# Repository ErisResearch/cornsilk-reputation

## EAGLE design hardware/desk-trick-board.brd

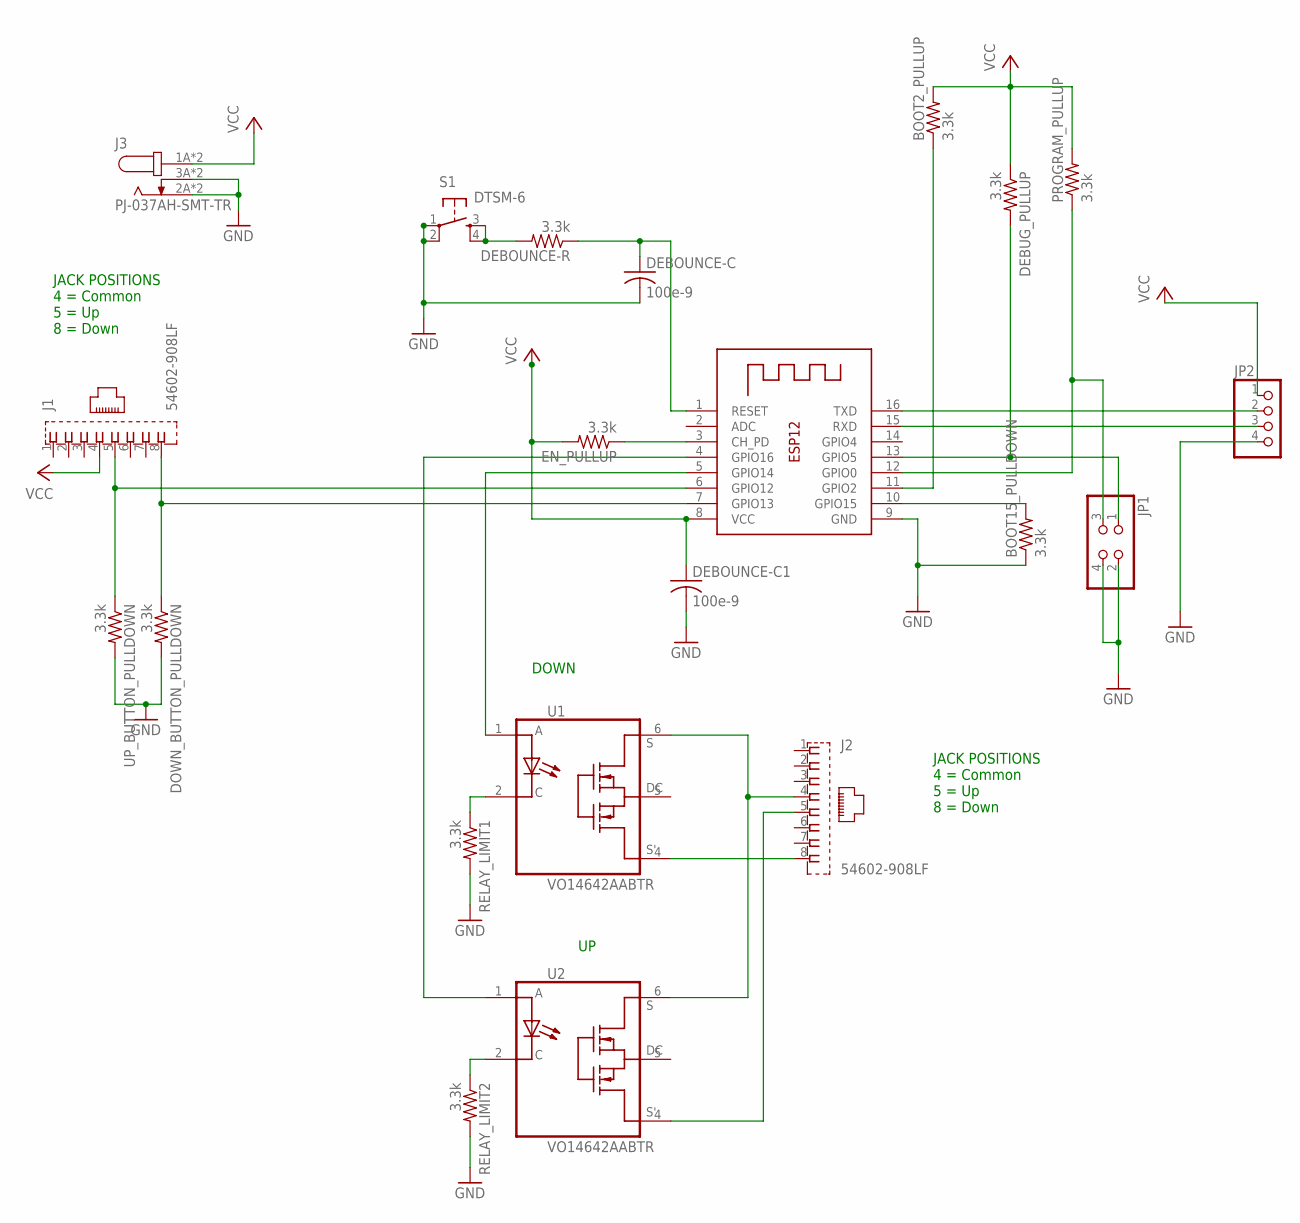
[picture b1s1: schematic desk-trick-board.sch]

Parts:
BOOT2_PULLUP, BOOT15_PULLDOWN: 3.3k; R0603
DEBOUNCE-C, DEBOUNCE-C1: 100e-9; C0603
DEBOUNCE-R: 3.3k; R0603
DEBUG_PULLUP: 3.3k; R0603
DOWN_BUTTON_PULLDOWN: 3.3k; R0603
EN_PULLUP: 3.3k; R0603
J1, J2: 54602-908LF; AMPHENOL_54602-908LF
J3: PJ-037AH-SMT-TR; CUI_PJ-037AH-SMT-TR
JP1: PINHD-2X2; 2X02
JP2: PINHD-1X4; 1X04
PROGRAM_PULLUP: 3.3k; R0603
RELAY_LIMIT1, RELAY_LIMIT2: 3.3k; R0603
S1: DTSM-6
U1, U2: VO14642AABTR; SOIC254P1005X390-6N
UP_BUTTON_PULLDOWN: 3.3k; R0603
X1: ESP-12

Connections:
BOOT2: BOOT2_PULLUP.1, X1.11 (GPIO2)
BOOT15: BOOT15_PULLDOWN.2, X1.10 (GPIO15)
DEBUG: DEBUG_PULLUP.2, JP1.1, X1.13 (GPIO5)
ESPRX: JP2.3, X1.15 (RXD)
ESPTX: JP2.2, X1.16 (TXD)
ESP_EN: EN_PULLUP.1, X1.3 (CH_PD)
GND: BOOT15_PULLDOWN.1, DEBOUNCE-C.2, DEBOUNCE-C1.2, DOWN_BUTTON_PULLDOWN.2, J3.2A (2), J3.2B (2), J3.3A (3), J3.3B (3), JP1.2, JP1.4, JP2.4, RELAY_LIMIT1.2, RELAY_LIMIT2.2, S1.1, S1.2, UP_BUTTON_PULLDOWN.2, X1.9 (GND)
IN_BD: DOWN_BUTTON_PULLDOWN.1, J1.8, X1.7 (GPIO13)
IN_BU: J1.5, UP_BUTTON_PULLDOWN.1, X1.6 (GPIO12)
unnamed: RELAY_LIMIT2.1, U2.2 (C)
unnamed: RELAY_LIMIT1.1, U1.2 (C)
unnamed: U1.1 (A), X1.5 (GPIO14)
unnamed: U2.1 (A), X1.4 (GPIO16)
OUT_BD: J2.8, U1.4 (S')
OUT_BU: J2.5, U2.4 (S')
OUT_COMMON: J2.4, U1.6 (S), U2.6 (S)
PROGRAM: JP1.3, PROGRAM_PULLUP.1, X1.12 (GPIO0)
RST: DEBOUNCE-C.1, DEBOUNCE-R.1, X1.1 (RESET)
RSTPRESS: DEBOUNCE-R.2, S1.3, S1.4
VCC: BOOT2_PULLUP.2, DEBOUNCE-C1.1, DEBUG_PULLUP.1, EN_PULLUP.2, J1.4, J3.1A (1), J3.1B (1), JP2.1, PROGRAM_PULLUP.2, X1.8 (VCC)

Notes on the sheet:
DOWN
JACK POSITIONS 4 = Common 5 = Up 8 = Down

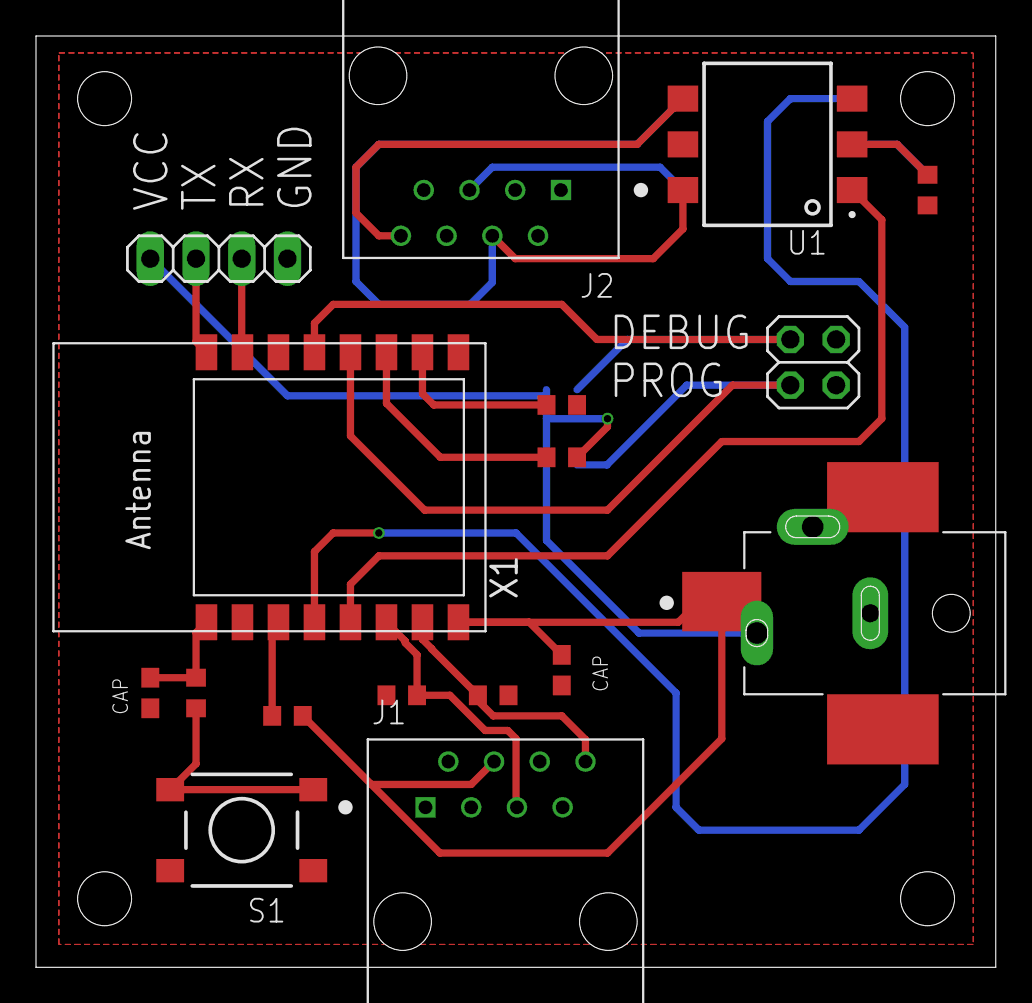
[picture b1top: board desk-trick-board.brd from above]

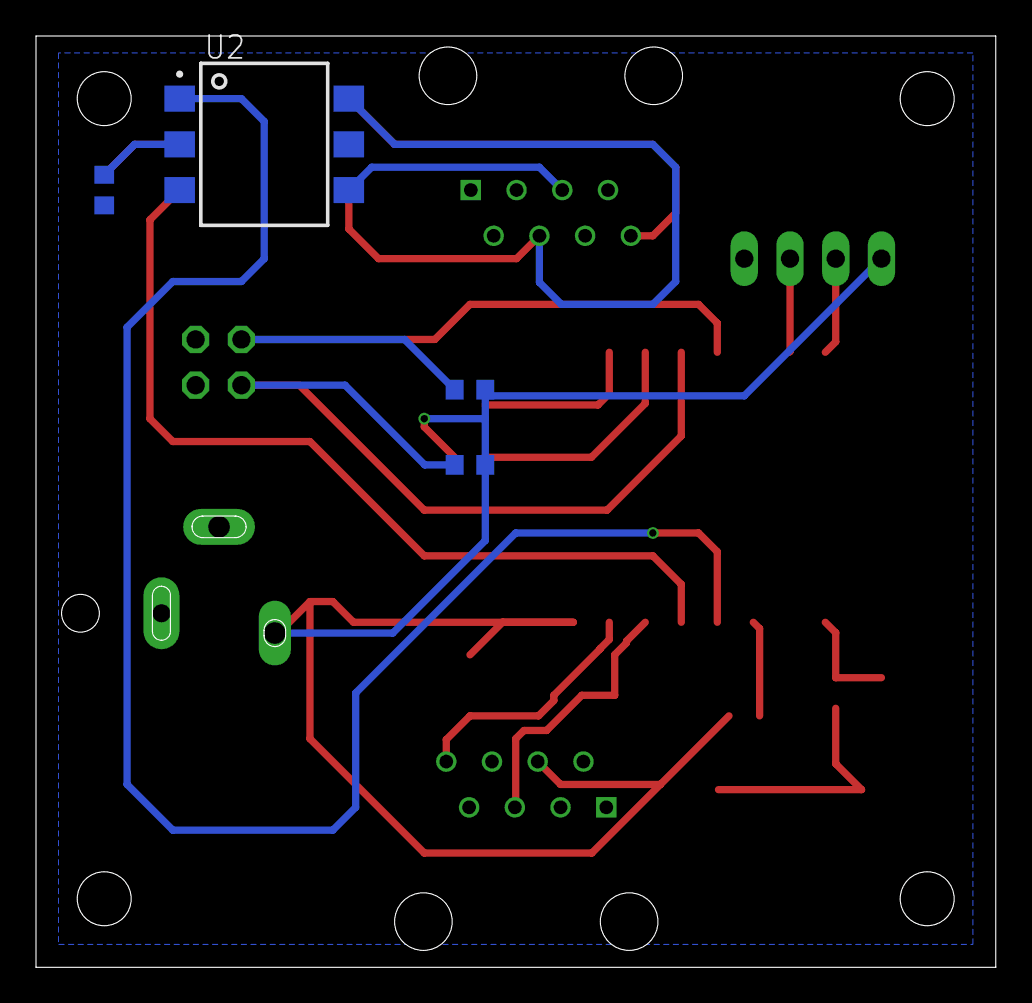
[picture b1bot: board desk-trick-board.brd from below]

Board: 2 copper layers, 53.3 x 51.7 mm, 21 parts (4 on the bottom side), 20 nets.

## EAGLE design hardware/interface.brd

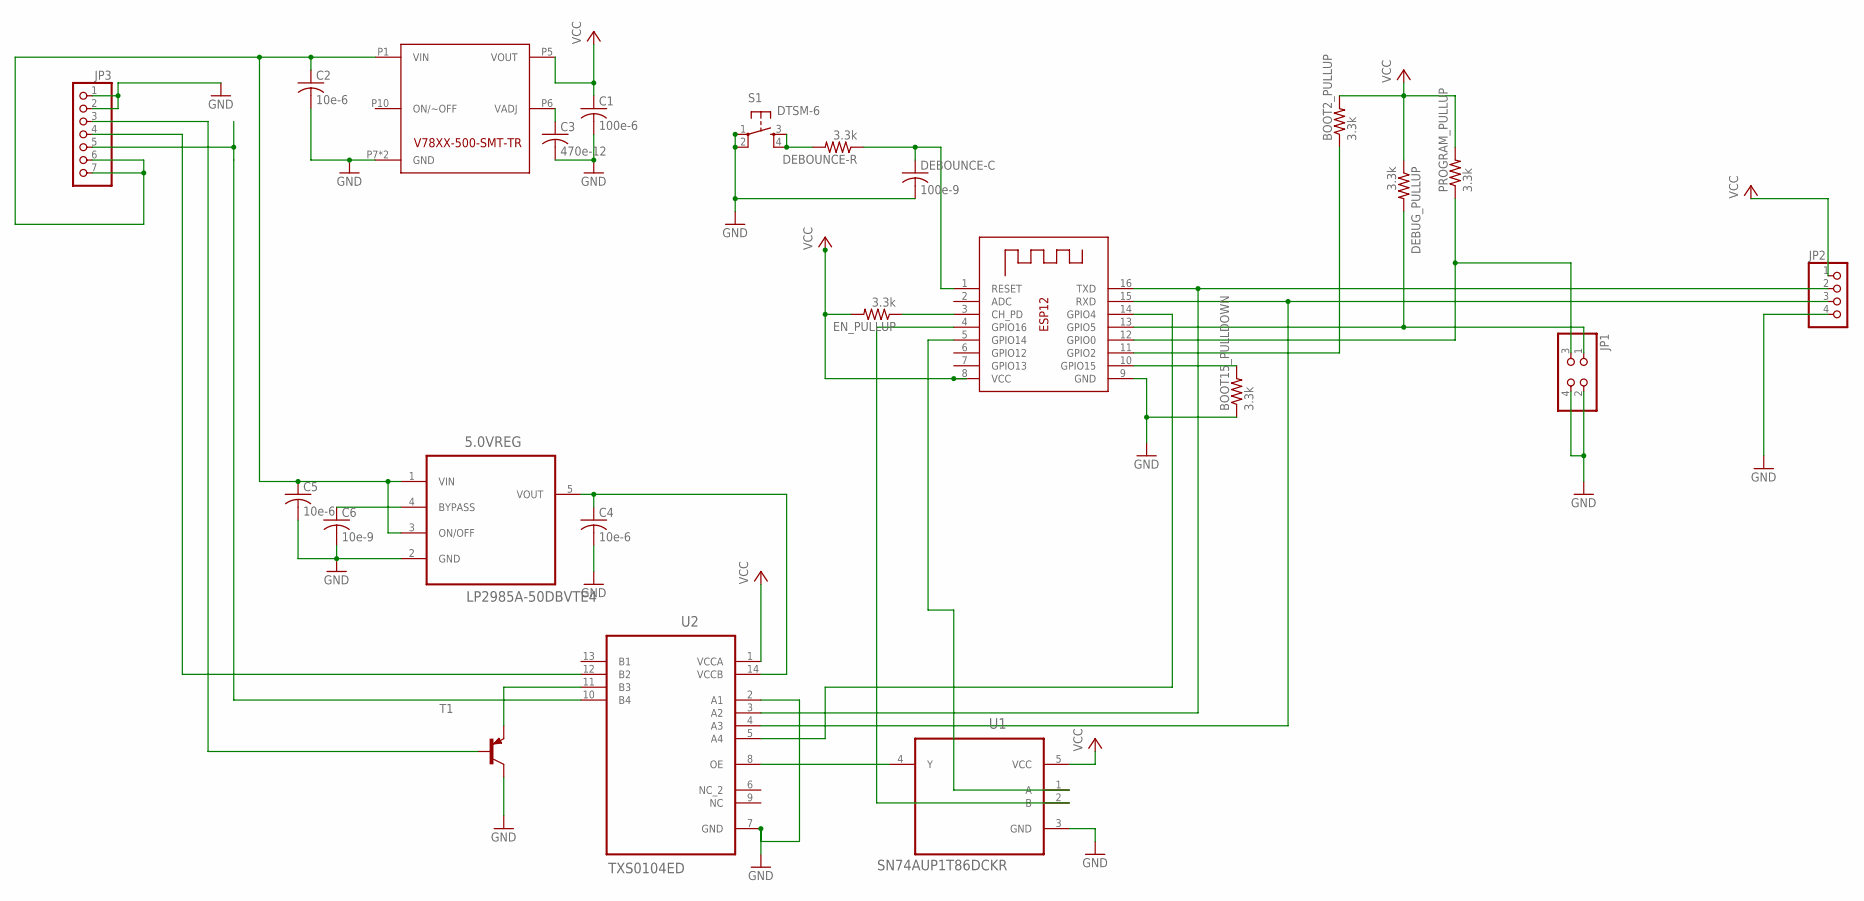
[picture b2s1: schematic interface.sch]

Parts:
5.0VREG: LP2985A-50DBVTE4; SOT95P280X145-5N
BOOT2_PULLUP, BOOT15_PULLDOWN: 3.3k; R0603
C1: 100e-6; C0603
C2, C4, C5: 10e-6; C0603
C3: 470e-12; C0603
C6: 10e-9; C0603
DEBOUNCE-C: 100e-9; C0603
DEBOUNCE-R: 3.3k; R0603
DEBUG_PULLUP: 3.3k; R0603
EN_PULLUP: 3.3k; R0603
JP1: PINHD-2X2; 2X02
JP2: PINHD-1X4; 1X04
JP3: PINHD-1X7; 1X07
PROGRAM_PULLUP: 3.3k; R0603
S1: DTSM-6
T1: MMBT2907ALT1-PNP-SOT23-BEC; SOT23-BEC
U1: SN74AUP1T86DCKR; SOT65P210X110-5N
U2: TXS0104ED; SOIC127P600X175-14N
U$1: V78XX-500-SMT-TR/SMD10-6; SMD-10/6
X1: ESP-12

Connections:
5VSUPPLY: 5.0VREG.5 (VOUT), C4.1, U2.14 (VCCB)
BATT+: 5.0VREG.1 (VIN), 5.0VREG.3 (ON/OFF), C2.1, C5.1, JP3.6, JP3.7, U$1.P1 (VIN)
BOOT2: BOOT2_PULLUP.1, X1.11 (GPIO2)
BOOT15: BOOT15_PULLDOWN.2, X1.10 (GPIO15)
DEBUG: DEBUG_PULLUP.2, JP1.1, X1.13 (GPIO5)
ESPBRC: U2.5 (A4), X1.14 (GPIO4)
ESPRX: JP2.3, U2.4 (A3), X1.15 (RXD)
ESPTX: JP2.2, U2.3 (A2), X1.16 (TXD)
GND: 5.0VREG.2 (GND), BOOT15_PULLDOWN.1, C1.2, C2.2, C3.2, C4.2, C5.2, C6.2, DEBOUNCE-C.2, JP1.2, JP1.4, JP2.4, JP3.1, JP3.2, S1.1, S1.2, T1.C, U1.3 (GND), U2.2 (A1), U2.7 (GND), U$1.P7 (GND), U$1.P9 (GND), X1.9 (GND)
unnamed: C3.1, U$1.P6 (VADJ)
unnamed: EN_PULLUP.1, X1.3 (CH_PD)
unnamed: 5.0VREG.4 (BYPASS), C6.1
unnamed: U1.2 (B), X1.4 (GPIO16)
unnamed: U1.1 (A), X1.5 (GPIO14)
PROGRAM: JP1.3, PROGRAM_PULLUP.1, X1.12 (GPIO0)
ROOMBABRC: JP3.5, U2.10 (B4)
ROOMBARX: JP3.4, U2.12 (B2)
ROOMBATX: JP3.3, T1.B
ROOMBATXBOOST: T1.E, U2.11 (B3)
RST: DEBOUNCE-C.1, DEBOUNCE-R.1, X1.1 (RESET)
RSTPRESS: DEBOUNCE-R.2, S1.3, S1.4
SERENABLE: U1.4 (Y), U2.8 (OE)
VCC: BOOT2_PULLUP.2, C1.1, DEBUG_PULLUP.1, EN_PULLUP.2, JP2.1, PROGRAM_PULLUP.2, U1.5 (VCC), U2.1 (VCCA), U$1.P5 (VOUT), X1.8 (VCC)

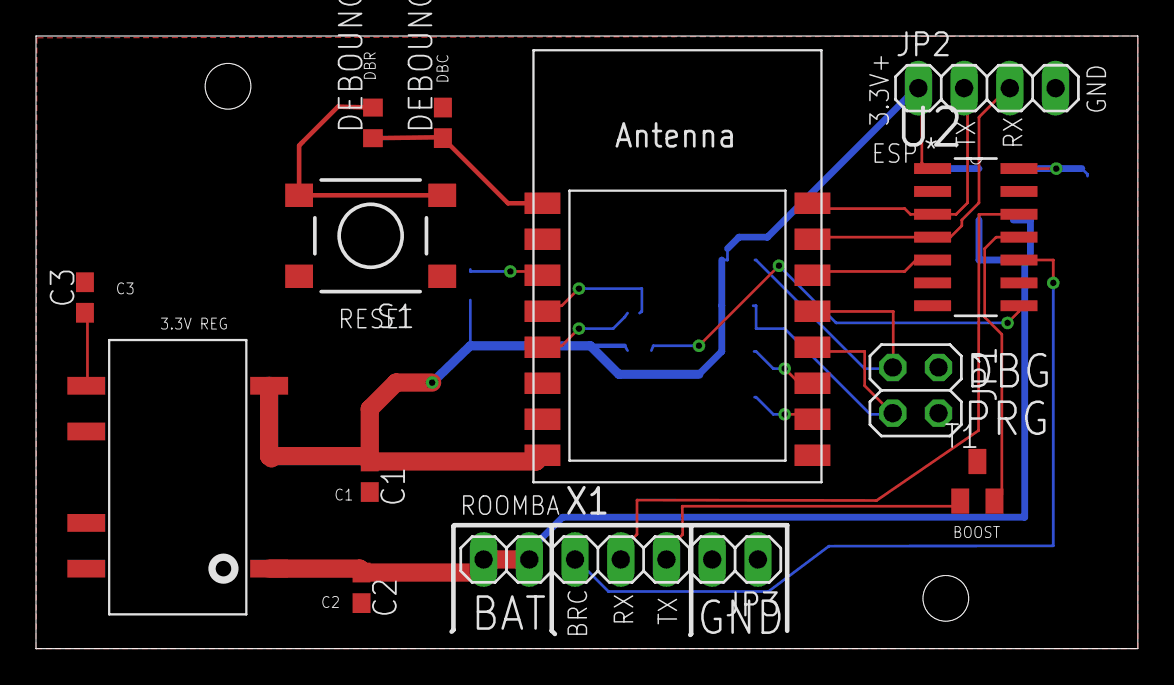
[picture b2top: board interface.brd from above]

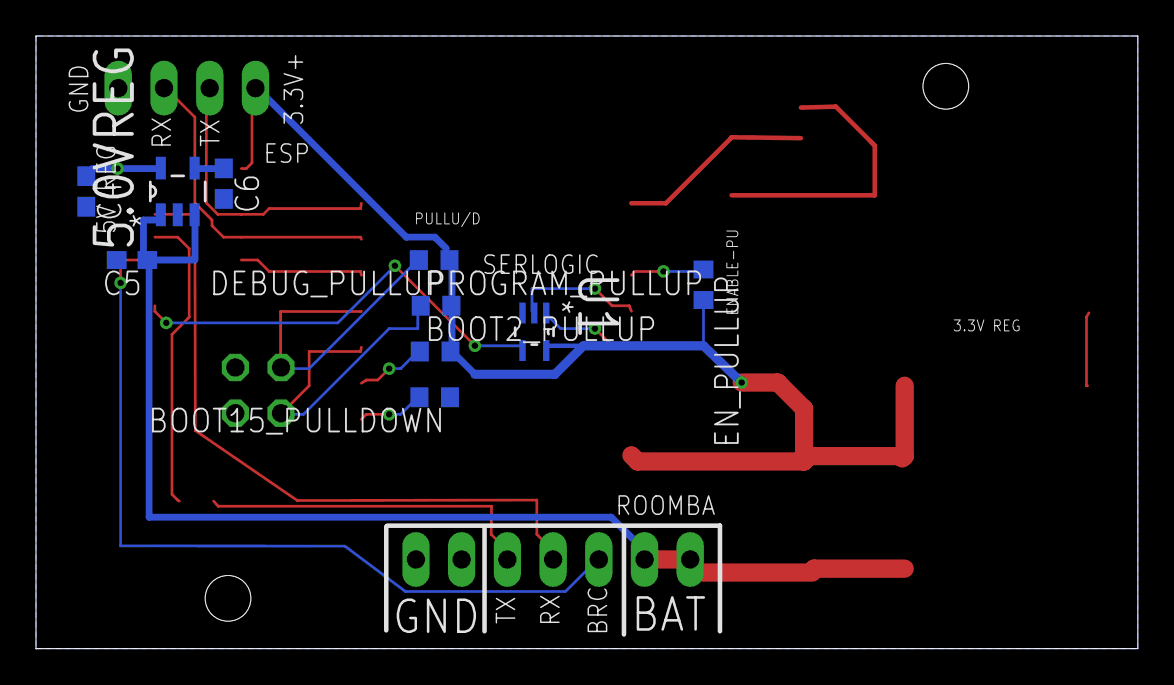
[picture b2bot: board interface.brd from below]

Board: 2 copper layers, 61.2 x 34.0 mm, 23 parts (10 on the bottom side), 23 nets.

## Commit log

2017-09-13 Add software from first revision
2017-09-13 Added eagle schematic and board for version 2
2017-09-16 Added sjson config parser
2017-09-16 Updated roombs serial control for board v2 (xor based enable)
2017-09-16 Updates for new NodeMCU API and use config.lua for storage management
2017-09-18 Fixed serial enable control
2017-09-28 Made a daily reboot and fixed the serial port remaining enabled at reboot
2017-09-28 Change when the serial translation is enabled to avoid any cross talk
2017-10-03 Simplified handling of MQTT messages to eliminate noise
2017-10-03 Set reset mask of the daily restart to work properly in Eastern time zone
2020-02-05 Initial rework for desk controller
2020-02-08 Fixed up MQTT, debug print functionality, and added an empty config
2020-02-08 Added debug prints for the control hook
2020-02-09 Limited desk rise time at start up due to GPIO being default high
2020-02-09 Added hardware files and nodemcu firmware
2020-02-22 Add stls for first crack at an enclosure
